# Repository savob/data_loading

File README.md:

# data_loading
Board inspired by the DATA album

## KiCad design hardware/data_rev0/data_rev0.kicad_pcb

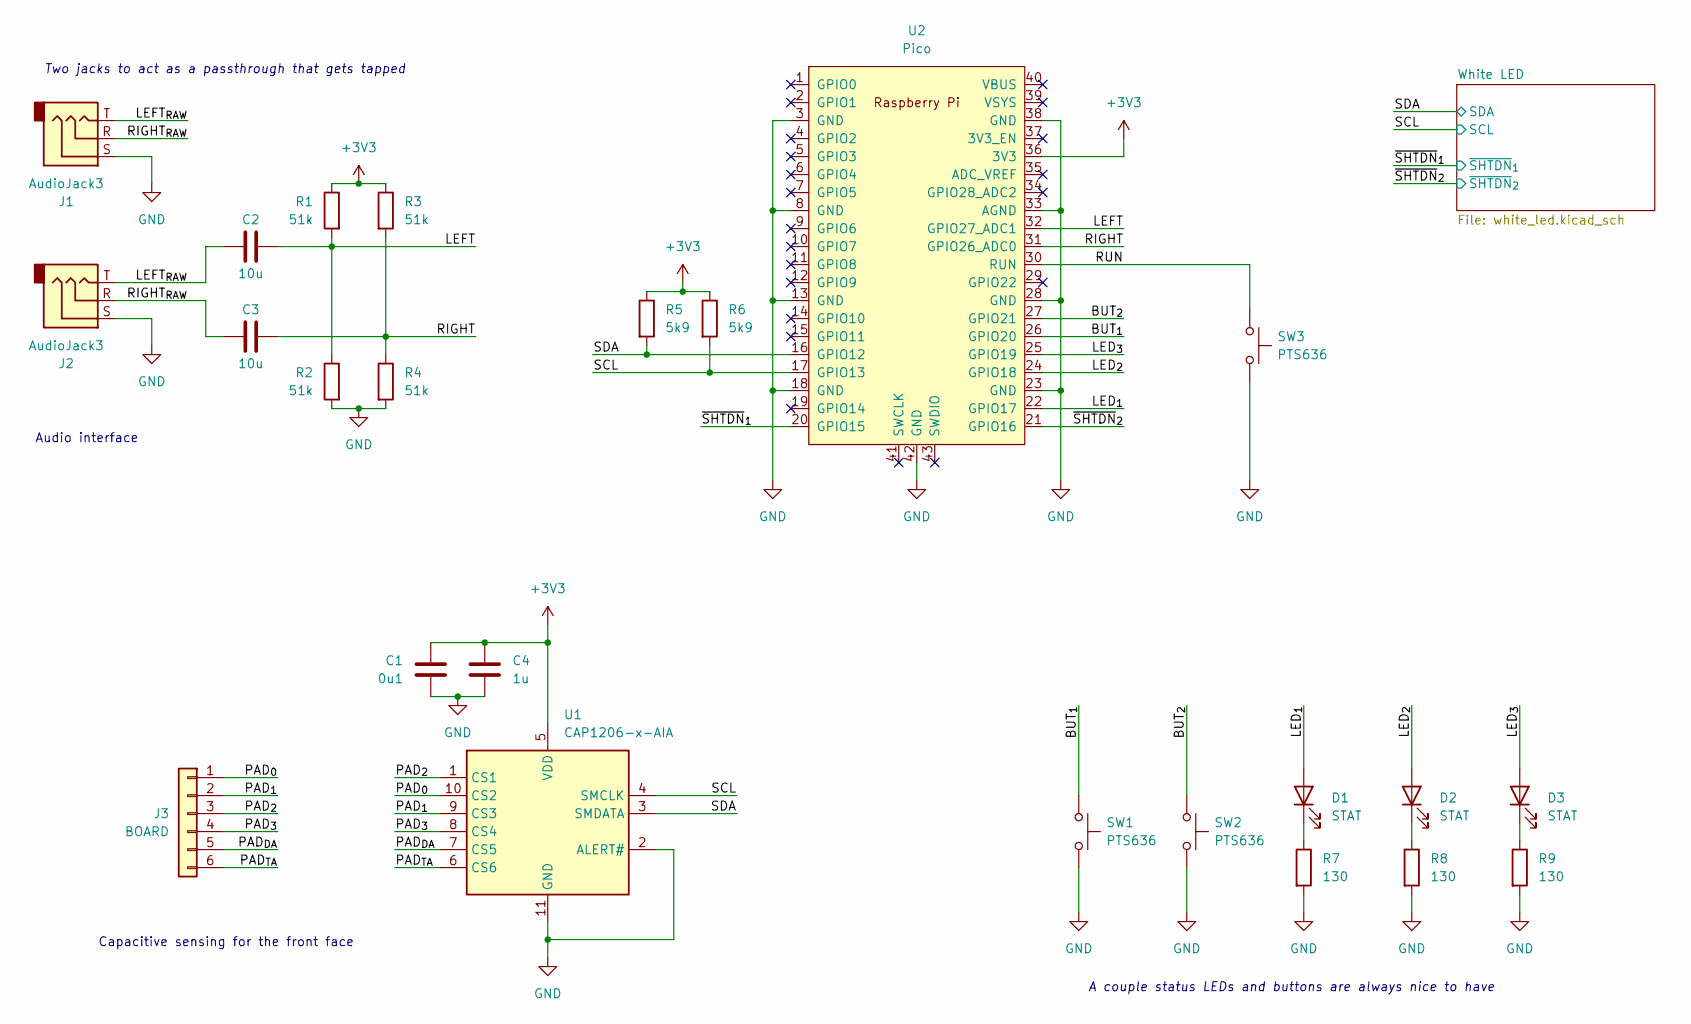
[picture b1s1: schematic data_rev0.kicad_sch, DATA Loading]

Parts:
C1: 0u1; C_0603_1608Metric
C2, C3: 10u; C_0805_2012Metric
C4: 1u; C_0603_1608Metric
D1, D2, D3: STAT; LED_0805_2012Metric
J1, J2: AudioJack3; Jack_3.5mm_CUI_SJ-3523-SMT_Horizontal
J3: BOARD; fill
R1, R2, R3, R4: 51k; R_0603_1608Metric
R5, R6: 5k9; R_0603_1608Metric
R7, R8, R9: 130; R_0603_1608Metric
SW1, SW2, SW3: PTS636; SW_SPST_CK_RS282G05A3
U1: CAP1206-x-AIA; DFN-10-1EP_3x3mm_P0.5mm_EP1.55x2.48mm
U2: Pico; RPi_Pico_SMD

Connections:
+3V3: C1.1, C4.2, R1.1, R3.1, R5.1, R6.1, U1.5 (VDD), U2.36 (3V3); also elsewhere on the board
/BUT_{1}: SW1.1, U2.26 (GPIO20)
/BUT_{2}: SW2.1, U2.27 (GPIO21)
/LED_{1}: D1.2 (A), U2.22 (GPIO17)
/LED_{2}: D2.2 (A), U2.24 (GPIO18)
/LED_{3}: D3.2 (A), U2.25 (GPIO19)
/LEFT: C2.1, R1.2, R2.1, U2.32 (GPIO27_ADC1)
/LEFT_{RAW}: C2.2, J1.T, J2.T
/PAD_{0}: J3.1, U1.10 (CS2)
/PAD_{1}: J3.2, U1.9 (CS3)
/PAD_{2}: J3.3, U1.1 (CS1)
/PAD_{3}: J3.4, U1.8 (CS4)
/PAD_{DA}: J3.5, U1.7 (CS5)
/PAD_{TA}: J3.6, U1.6 (CS6)
/RIGHT: C3.1, R3.2, R4.1, U2.31 (GPIO26_ADC0)
/RIGHT_{RAW}: C3.2, J1.R, J2.R
/RUN: SW3.1, U2.30 (RUN)
/SCL: R6.2, U1.4 (SMCLK), U2.17 (GPIO13); also elsewhere on the board
/SDA: R5.2, U1.3 (SMDATA), U2.16 (GPIO12); also elsewhere on the board
/~SHTDN_{1}: U2.20 (GPIO15); also elsewhere on the board
/~SHTDN_{2}: U2.21 (GPIO16); also elsewhere on the board
GND: C1.2, C4.1, J1.S, J2.S, R2.2, R4.2, R7.2, R8.2, R9.2, SW1.2, SW2.2, SW3.2, U1.2 (ALERT#), U1.11 (GND), U2.3 (GND), U2.8 (GND), U2.13 (GND), U2.18 (GND), U2.23 (GND), U2.28 (GND), U2.33 (AGND), U2.38 (GND), U2.42 (GND); also elsewhere on the board
unnamed: D1.1 (K), R7.1
unnamed: D2.1 (K), R8.1
unnamed: D3.1 (K), R9.1

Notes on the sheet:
A couple status LEDs and buttons are always nice to have
Two jacks to act as a passthrough that gets tapped
Audio interface
Capacitive sensing for the front face

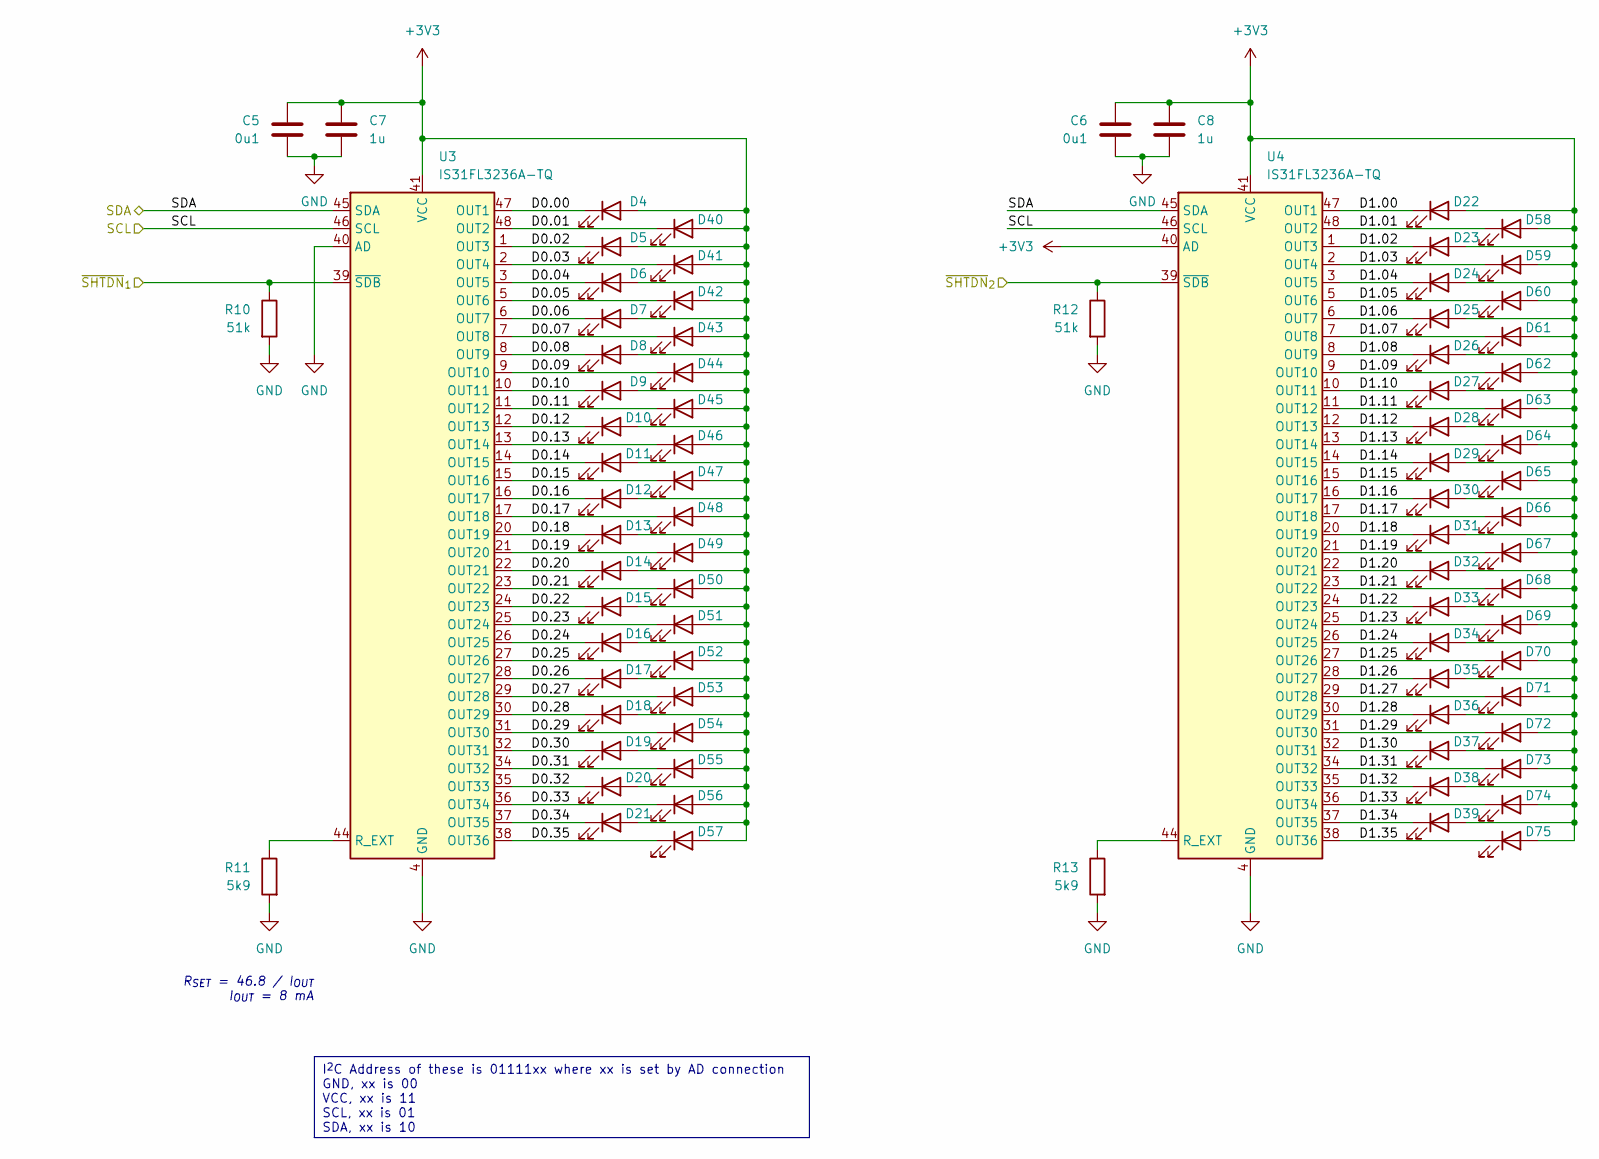
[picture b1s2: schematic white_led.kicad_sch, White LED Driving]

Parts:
C5, C6: 0u1; C_0603_1608Metric
C7, C8: 1u; C_0603_1608Metric
D4, D5, D6, D7, D8, D9, D10, D11, D12, D13, D14, D15, D16, D17, D18, D19, D20, D21, D22, D23, D24, D25, D26, D27, D28, D29, D30, D31, D32, D33, D34, D35, D36, D37, D38, D39: LED; D_0805_2012Metric
D40, D41, D42, D43, D44, D45, D46, D47, D48, D49, D50, D51, D52, D53, D54, D55, D56, D57, D58, D59, D60, D61, D62, D63, D64, D65, D66, D67, D68, D69, D70, D71, D72, D73, D74, D75: LED_RA; D_1206_3216Metric
R10, R12: 51k; R_0603_1608Metric
R11, R13: 5k9; R_0603_1608Metric
U3, U4: IS31FL3236A-TQ; TQFP-48-1EP_7x7mm_P0.5mm_EP4.11x4.11mm

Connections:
+3V3: C5.1, C6.1, C7.1, C8.1, D4.2 (A), D5.2 (A), D6.2 (A), D7.2 (A), D8.2 (A), D9.2 (A), D10.2 (A), D11.2 (A), D12.2 (A), D13.2 (A), D14.2 (A), D15.2 (A), D16.2 (A), D17.2 (A), D18.2 (A), D19.2 (A), D20.2 (A), D21.2 (A), D22.2 (A), D23.2 (A), D24.2 (A), D25.2 (A), D26.2 (A), D27.2 (A), D28.2 (A), D29.2 (A), D30.2 (A), D31.2 (A), D32.2 (A), D33.2 (A), D34.2 (A), D35.2 (A), D36.2 (A), D37.2 (A), D38.2 (A), D39.2 (A), D40.2 (A), D41.2 (A), D42.2 (A), D43.2 (A), D44.2 (A), D45.2 (A), D46.2 (A), D47.2 (A), D48.2 (A), D49.2 (A), D50.2 (A), D51.2 (A), D52.2 (A), D53.2 (A), D54.2 (A), D55.2 (A), D56.2 (A), D57.2 (A), D58.2 (A), D59.2 (A), D60.2 (A), D61.2 (A), D62.2 (A), D63.2 (A), D64.2 (A), D65.2 (A), D66.2 (A), D67.2 (A), D68.2 (A), D69.2 (A), D70.2 (A), D71.2 (A), D72.2 (A), D73.2 (A), D74.2 (A), D75.2 (A), U3.41 (VCC), U4.40 (AD), U4.41 (VCC); also elsewhere on the board
/SCL: U3.46 (SCL), U4.46 (SCL); also elsewhere on the board
/SDA: U3.45 (SDA), U4.45 (SDA); also elsewhere on the board
/White LED/D0.00: D4.1 (K), U3.47 (OUT1)
/White LED/D0.01: D40.1 (K), U3.48 (OUT2)
/White LED/D0.02: D5.1 (K), U3.1 (OUT3)
/White LED/D0.03: D41.1 (K), U3.2 (OUT4)
/White LED/D0.04: D6.1 (K), U3.3 (OUT5)
/White LED/D0.05: D42.1 (K), U3.5 (OUT6)
/White LED/D0.06: D7.1 (K), U3.6 (OUT7)
/White LED/D0.07: D43.1 (K), U3.7 (OUT8)
/White LED/D0.08: D8.1 (K), U3.8 (OUT9)
/White LED/D0.09: D44.1 (K), U3.9 (OUT10)
/White LED/D0.10: D9.1 (K), U3.10 (OUT11)
/White LED/D0.11: D45.1 (K), U3.11 (OUT12)
/White LED/D0.12: D10.1 (K), U3.12 (OUT13)
/White LED/D0.13: D46.1 (K), U3.13 (OUT14)
/White LED/D0.14: D11.1 (K), U3.14 (OUT15)
/White LED/D0.15: D47.1 (K), U3.15 (OUT16)
/White LED/D0.16: D12.1 (K), U3.16 (OUT17)
/White LED/D0.17: D48.1 (K), U3.17 (OUT18)
/White LED/D0.18: D13.1 (K), U3.20 (OUT19)
/White LED/D0.19: D49.1 (K), U3.21 (OUT20)
/White LED/D0.20: D14.1 (K), U3.22 (OUT21)
/White LED/D0.21: D50.1 (K), U3.23 (OUT22)
/White LED/D0.22: D15.1 (K), U3.24 (OUT23)
/White LED/D0.23: D51.1 (K), U3.25 (OUT24)
/White LED/D0.24: D16.1 (K), U3.26 (OUT25)
/White LED/D0.25: D52.1 (K), U3.27 (OUT26)
/White LED/D0.26: D17.1 (K), U3.28 (OUT27)
/White LED/D0.27: D53.1 (K), U3.29 (OUT28)
/White LED/D0.28: D18.1 (K), U3.30 (OUT29)
/White LED/D0.29: D54.1 (K), U3.31 (OUT30)
/White LED/D0.30: D19.1 (K), U3.32 (OUT31)
/White LED/D0.31: D55.1 (K), U3.34 (OUT32)
/White LED/D0.32: D20.1 (K), U3.35 (OUT33)
/White LED/D0.33: D56.1 (K), U3.36 (OUT34)
/White LED/D0.34: D21.1 (K), U3.37 (OUT35)
/White LED/D0.35: D57.1 (K), U3.38 (OUT36)
/White LED/D1.00: D22.1 (K), U4.47 (OUT1)
/White LED/D1.01: D58.1 (K), U4.48 (OUT2)
/White LED/D1.02: D23.1 (K), U4.1 (OUT3)
/White LED/D1.03: D59.1 (K), U4.2 (OUT4)
/White LED/D1.04: D24.1 (K), U4.3 (OUT5)
/White LED/D1.05: D60.1 (K), U4.5 (OUT6)
/White LED/D1.06: D25.1 (K), U4.6 (OUT7)
/White LED/D1.07: D61.1 (K), U4.7 (OUT8)
/White LED/D1.08: D26.1 (K), U4.8 (OUT9)
/White LED/D1.09: D62.1 (K), U4.9 (OUT10)
/White LED/D1.10: D27.1 (K), U4.10 (OUT11)
/White LED/D1.11: D63.1 (K), U4.11 (OUT12)
/White LED/D1.12: D28.1 (K), U4.12 (OUT13)
/White LED/D1.13: D64.1 (K), U4.13 (OUT14)
/White LED/D1.14: D29.1 (K), U4.14 (OUT15)
/White LED/D1.15: D65.1 (K), U4.15 (OUT16)
/White LED/D1.16: D30.1 (K), U4.16 (OUT17)
/White LED/D1.17: D66.1 (K), U4.17 (OUT18)
/White LED/D1.18: D31.1 (K), U4.20 (OUT19)
/White LED/D1.19: D67.1 (K), U4.21 (OUT20)
/White LED/D1.20: D32.1 (K), U4.22 (OUT21)
/White LED/D1.21: D68.1 (K), U4.23 (OUT22)
/White LED/D1.22: D33.1 (K), U4.24 (OUT23)
/White LED/D1.23: D69.1 (K), U4.25 (OUT24)
/White LED/D1.24: D34.1 (K), U4.26 (OUT25)
/White LED/D1.25: D70.1 (K), U4.27 (OUT26)
/White LED/D1.26: D35.1 (K), U4.28 (OUT27)
/White LED/D1.27: D71.1 (K), U4.29 (OUT28)
/White LED/D1.28: D36.1 (K), U4.30 (OUT29)
/White LED/D1.29: D72.1 (K), U4.31 (OUT30)
/White LED/D1.30: D37.1 (K), U4.32 (OUT31)
/White LED/D1.31: D73.1 (K), U4.34 (OUT32)
/White LED/D1.32: D38.1 (K), U4.35 (OUT33)
/White LED/D1.33: D74.1 (K), U4.36 (OUT34)
/White LED/D1.34: D39.1 (K), U4.37 (OUT35)
/White LED/D1.35: D75.1 (K), U4.38 (OUT36)
/~SHTDN_{1}: R10.1, U3.39 (~SDB); also elsewhere on the board
/~SHTDN_{2}: R12.1, U4.39 (~SDB); also elsewhere on the board
GND: C5.2, C6.2, C7.2, C8.2, R10.2, R11.2, R12.2, R13.2, U3.4 (GND), U3.18 (GND), U3.19 (GND), U3.33 (GND), U3.40 (AD), U3.42 (GND), U3.43 (GND), U3.49 (GND), U4.4 (GND), U4.18 (GND), U4.19 (GND), U4.33 (GND), U4.42 (GND), U4.43 (GND), U4.49 (GND); also elsewhere on the board
unnamed: R11.1, U3.44 (R_EXT)
unnamed: R13.1, U4.44 (R_EXT)

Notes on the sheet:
I^{2}C Address of these is 01111xx where xx is set by AD connection GND, xx is 00 VCC, xx is 11 SCL, xx is 01 SDA, xx is 10
R_{SET} = 46.8 / I_{OUT} I_{OUT} = 8 mA

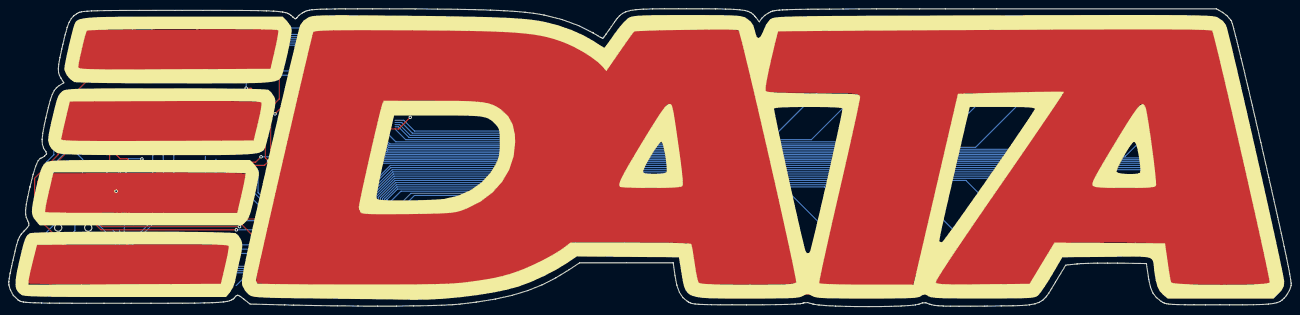
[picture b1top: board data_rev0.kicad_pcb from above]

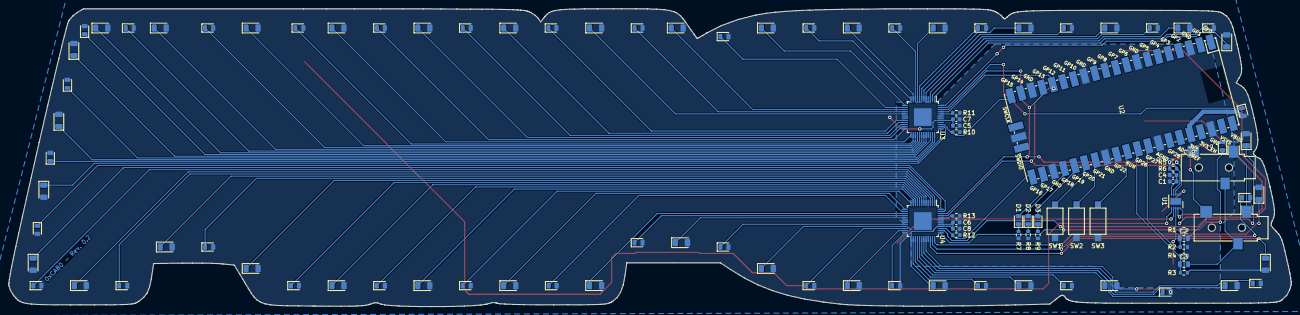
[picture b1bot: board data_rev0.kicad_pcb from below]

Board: 2 copper layers, 298.7 x 69.4 mm, 106 parts (105 on the bottom side), 99 nets.

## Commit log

2024-02-15 Initialization of hardware project
2024-02-15 Added subsheets for rev 1
2024-02-17 Initial layout and circuit
2024-02-17 Removed unnecessary files
2024-02-17 Moved audio jacks to the side. Ordered.
2024-02-17 Added ordered gerber filed
2024-02-17 Changed name of gerber archive
2024-02-19 Upped the IC revision for the LED driver to IS31FL3236*A*
2024-02-19 Finalized BOM
2024-02-22 Started firmware project
    Lightly modified code for an RPi Pico spectrum analyzer http://radiopench.blog96.fc2.com/. Stripped out the code related to running it's display.
2024-02-22 Converted to non-depreciated functions
2024-02-22 Added address note for LED drivers
2024-02-22 Initial LED driver library
2024-02-22 Refactored transfer status constants
2024-02-22 Minor formatting
2024-02-22 Initial touch sensor library
2024-02-23 Added labels for LED lines
2024-02-23 Initial LED library
    Also moved gamma constants fromm drivers to LED calculation
2024-02-23 Cleared DRC exceptions
2024-02-23 Touched up initial LED committed
    Shifted from specifying the step period for effect to the overall period so they're easier to tune.
    Added `typedef`s for easier optimization later.
2024-02-23 Added LED helper functions
2024-02-23 Added rotating effect code
2024-02-23 Changed "@" to "\" for deoxygen comments
2024-02-23 Minor FSM fix
2024-02-24 Added direction parameter to rotation effect
2024-02-25 Added wave LED effects
2024-02-26 Touch ups
    Lots of small changes and fixes:
    - Fixed when `nextMark` is updated so resets can actually be detected
    - Added an `if` statement for noticing changing states in the FSM
    - Fixed some comments
    - Added helper functions/variables for gamma-corrected LED level operation
2024-02-26 Added cloud effect
2024-02-26 Made index contrainer flexible, moved defaults to `.cpp`
2024-02-26 Moved defaults to `.cpp`
2024-02-26 Added initial tracking effect
2024-02-26 Added tracking to LED FSM
2024-02-26 Added LED FSM to main loop
2024-02-27 Removed auto-initialization
2024-02-27 Fixed LED driver addresses
2024-02-27 Moved audio to library
2024-02-27 Working CAP1206 committed
    Made several small fixes that contributed to the CAP1206 now working:
    - Read transactions should not be stopped after register address write
    - Added additional error checking for I2C transfers
    - Autoclear interrupt flag for CAP on reads so the sensors would detect release
    - Added functions for checking device characteristics (ID, Manufacturer, Rev). *Useful for tests.*
    - Added `readDelta` function
2024-02-27 Added CAP1206 to main loop
    Also changed indent on `main.cpp` from two to four spaces for consistency with other files.
2024-02-27 Moved to KiCad 8.0.0
    Also added value for right angle LEDs toi be seperate of the head on ones
2024-02-28 Upped Baudrate
    Shouldn't really effect anything since it's a direct USB connection.
2024-02-28 Excluded most parts from simulation
2024-02-28 Initial audio driver
2024-02-29 Adjusted startup order
2024-02-29 Fixed column/row painting math
    Also broke some long lines to reduce need for horizontal scrolling.
2024-02-29 Got wave effects working
    Touched up reset function to account for audio sampling time to prevent continuous resets if the audio sampling takes much longer than the function is meant to run.
    Also changed LED constants to all caps to make them clear in the code.
2024-02-29 Fixed cloud mode
2024-02-29 Got tracking effect working
2024-02-29 Made swaps static for porper operation
2024-02-29 Added interrupt check for pads
    This way single and repeat events are properly picked up.
    Also broke long lines in the CAP1206 library.
2024-03-01 Added LED rotation function
    Also refactored code for LEDs a bit and the moved the defaults for functions to the `.hpp`
2024-03-01 Capitalized constants in spin function, removed unused variable
2024-03-01 Bump LED effect complete
2024-03-01 Integrated capacitive pads for LED FSM control
    Had to rework some of the logic for the CAP sensor to avoid recording release events.
2024-03-01 Improved LED gamma system
    Main intent was to improve the colour inversion. Also merged `uniformLED` and `uniformGamma` for easier maintenance.
2024-03-01 Improved rcolumn/row painting functions
    There was an indexing error in the row painting for LED[0].
    Changed their logic to use an generic pointer so updating the same logic for different faces applies to both gamma and brightness.
2024-03-01 Fixed write to CONFIG 2
    This allowed releases to be properly ignored, so I reimplemented the repeated press events.
    Also added comments to parameters in the initialization function for the parameters.
2024-03-01 Slowed down setup
2024-03-01 Uniform audio intensity effect complete
    Sampling audio really slows down the other effects. I should look into putting that on a seperate core from the lighting effect.
2024-03-01 Added balance LED effect
2024-03-01 Added conditions for audio sampling
2024-03-01 Added horizontal spectrum graph
2024-03-01 Fixed `filterSpectrum` reading out of bounds
2024-03-01 Added split spectrum effect
2024-03-01 Add spinning split
2024-03-01 Boosted scaling of RMS effects
2024-03-02 Added vertical volume effect
2024-03-02 Added horizontal volume effect
2024-03-02 Fixed reversing direction for volume bars
    Volume peaks marks were not being reversed proply when mirrored
2024-03-02 Added split horizontal volume bar
2024-03-02 Added comment
2024-03-03 Fixed direction change freezing for wave effects
2024-03-03 Tidied up setup
2024-03-03 Fixed rotation effect recovery
    Due to the prior simple set up for rotation, recovering after a colour inversion caused the bumps to get too long
2024-03-04 Proper LED driver setup
2024-03-04 Changed SOLID LED to allow brightness control
2024-03-04 Removed redundant driver initialization
2024-03-04 Added Rev 0 project
    Started some of my changes on Rev 1. Also changed the RP Pico footprint to have solderpaste on the pads.
2024-03-04 Added random incrementing to CLOUD and TRACKING
2024-03-04 Added sweeping effect
2024-03-04 Added swaying effect
2024-03-04 Changed LED to use only gamma levels
    This was done to simplify code and make it easier for proper inversion to be done.
2024-03-05 Demo tweeks
2024-03-05 Tweeked sweep logic
2024-03-05 Moved sample preprocessing to sampling block
2024-03-05 Added check to see if LED updates were necessary
    Might try to make it smarter in the future to specifically target regiseters if only a couple need changing instead of writing the entire buffer.
2024-03-05 Added time measurements
2024-03-10 Added gamma to initialization
2024-03-10 Added forced update of LED duties on initialization
2024-03-10 Added watchdog timer feature
2024-03-10 Sped up setup
2024-03-10 Adjusted touch sensitivity
    Adjusted capacitive sensing senisitivity so it wasn't saturating, needed to be stepped down by a factor of 16!
    Now a finger press is about 70 to 75. Should be much more resistant to noise/interference from other circuitry.
    Also fixed the `readDelta` function to properly read the deltas as signed values.
2024-03-10 Put watchdog as first thing in setup
2024-03-10 Made loudness more responsive
    Moved checks for upper marker to be done everytime the effect is run, rather than periodically. The result is a more responsive effect.
2024-03-15 Reduced threshold for contact
2024-03-15 Touched up audio balance effect
    Now there's a block that tracks the balance and volume instead of a gradient. Way more perceptible now with normal music!
2024-03-15 Made function for overall RMS calculation
2024-03-15 Removed accidental double default declaration
2024-03-15 Added ability to ignore bottom frequencies
    Since the bottom frequency buckets generally hold non-zero values due to DC components in the FFT they messed up the visuals by always being on.
2024-03-15 Made `SerialUSB` explicit
    Also fixed minor spelling error for shifting enumerator
2024-03-15 Added periodic capacitive sensor recalibration in inactivity
2024-03-15 Raised thresholds from testing
2024-03-15 Added delay to non-audio loops
    This seems to make the contact pads/capacitive system more responsive in non-audio modes.
    Probably due to the contact sensor being continuously pooled since Rev. 0 doesn't use its interrupt pin.
2024-03-15 Changed touch sensor to be periodically polled
    This is better for the LED effects compared to a delay for each loop cycle
2024-03-18 Reworked audio sample control
    Allow for more granular audio processing increments. Some modes need none, others just RMS and then few the actual spectrum which takes a lot of time to aquire.
2024-03-18 Added "debug" environment
